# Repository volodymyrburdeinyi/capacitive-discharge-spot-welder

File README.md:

# capacitive-discharge-spot-welder
Capacitive discharge spot welder based on KEKK K100 controller board.

# software 
KiCad 7.0.

# BOM
See pot_welder.kicad_sch schematic.

# KEKK K100
Replace the linear 5V regulator on the KEKK K100 board with a more effitient switching regulator.
This will reduce the number of shutdowns due to main capacitors bank discharche after welding.

# references 
 - https://hackaday.io/project/187652-not-so-smart-capacitive-discharge-spot-welder

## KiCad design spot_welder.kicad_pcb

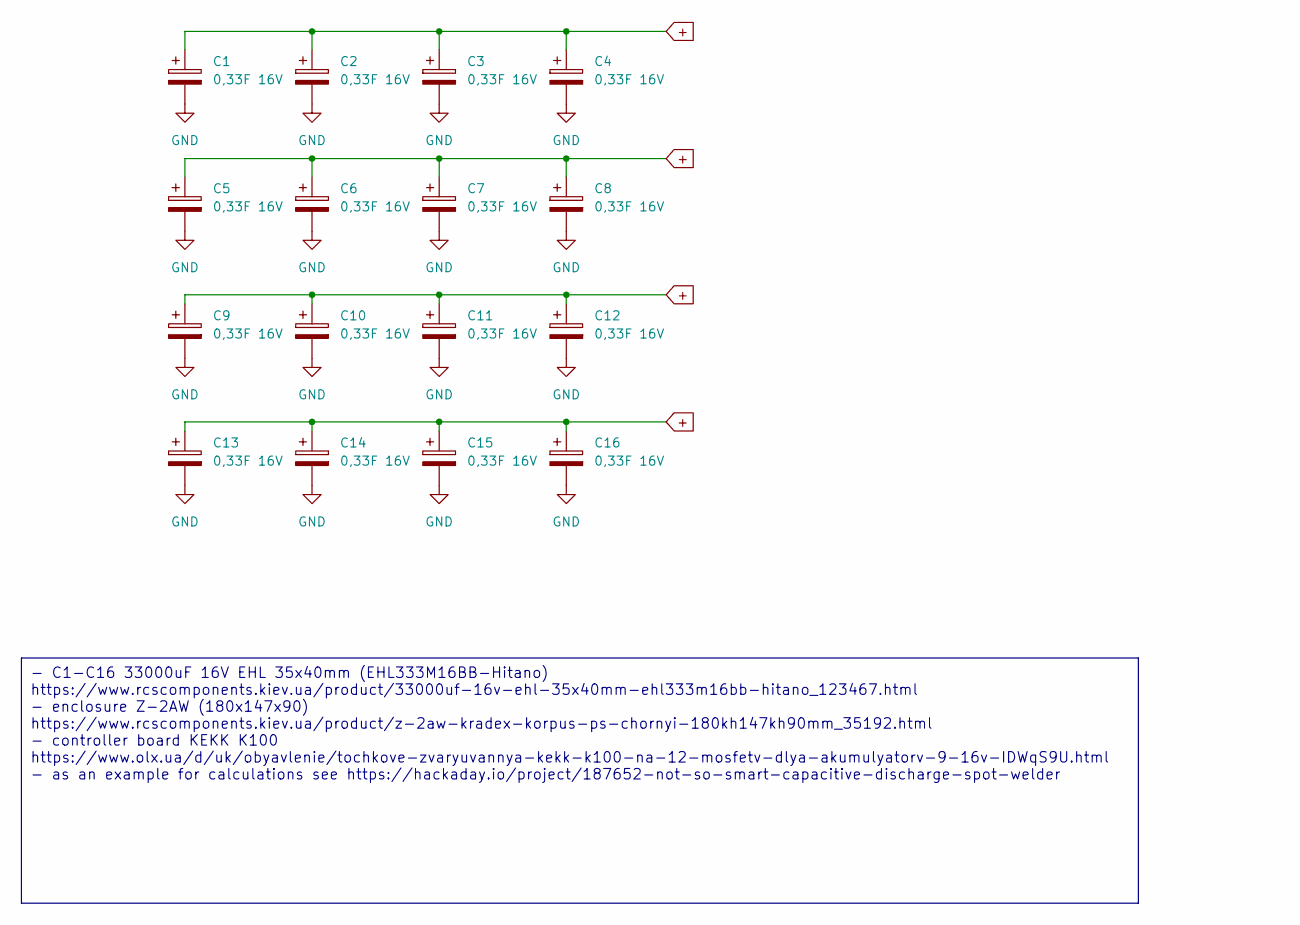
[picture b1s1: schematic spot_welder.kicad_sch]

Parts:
C1, C2, C3, C4, C5, C6, C7, C8, C9, C10, C11, C12, C13, C14, C15, C16: 0,33F 16V; CP_Radial_D35.0mm_P10.00mm_SnapIn

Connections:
+: C1.1, C2.1, C3.1, C4.1, C5.1, C6.1, C7.1, C8.1, C9.1, C10.1, C11.1, C12.1, C13.1, C14.1, C15.1, C16.1
GND: C1.2, C2.2, C3.2, C4.2, C5.2, C6.2, C7.2, C8.2, C9.2, C10.2, C11.2, C12.2, C13.2, C14.2, C15.2, C16.2

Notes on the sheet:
- C1-C16 33000uF 16V EHL 35x40mm (EHL333M16BB-Hitano) https://www.rcscomponents.kiev.ua/product/33000uf-16v-ehl-35x40mm-ehl333m16bb-hitano_123467.html - enclosure Z-2AW (180х147х90) https://www.rcscomponents.kiev.ua/product/z-2aw-kradex-korpus-ps-chornyi-180kh147kh90mm_35192.html - controller board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

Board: 2 copper layers, 16 parts (0 on the bottom side), 2 nets, no tracks yet.

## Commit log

2024-06-16 feat: first working version
